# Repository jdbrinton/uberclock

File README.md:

# UberClock PCB
This is the PCB design for the Crystal Filter for the UberClock multi-mode oscillator.

To download gerber files, schematics, or other documentation, see [Latest Release](https://github.com/jdbrinton/uberclock/releases).

# Details
Board dimensions: 100x100mm

Tools: Altium Designer Professional (23.11.1)

# Errata
1. See [issue #1](https://github.com/jdbrinton/uberclock/issues/1) for details and resolution. Crystal resonator footprint wrong. Pin numbers are mirrored.

# Measurements

Measurements taken on NanoVNA V2 (https://nanorfe.com/nanovna-v2.html)

# Sponsor

This work received donation from: https://nlnet.nl/project/uberClock/

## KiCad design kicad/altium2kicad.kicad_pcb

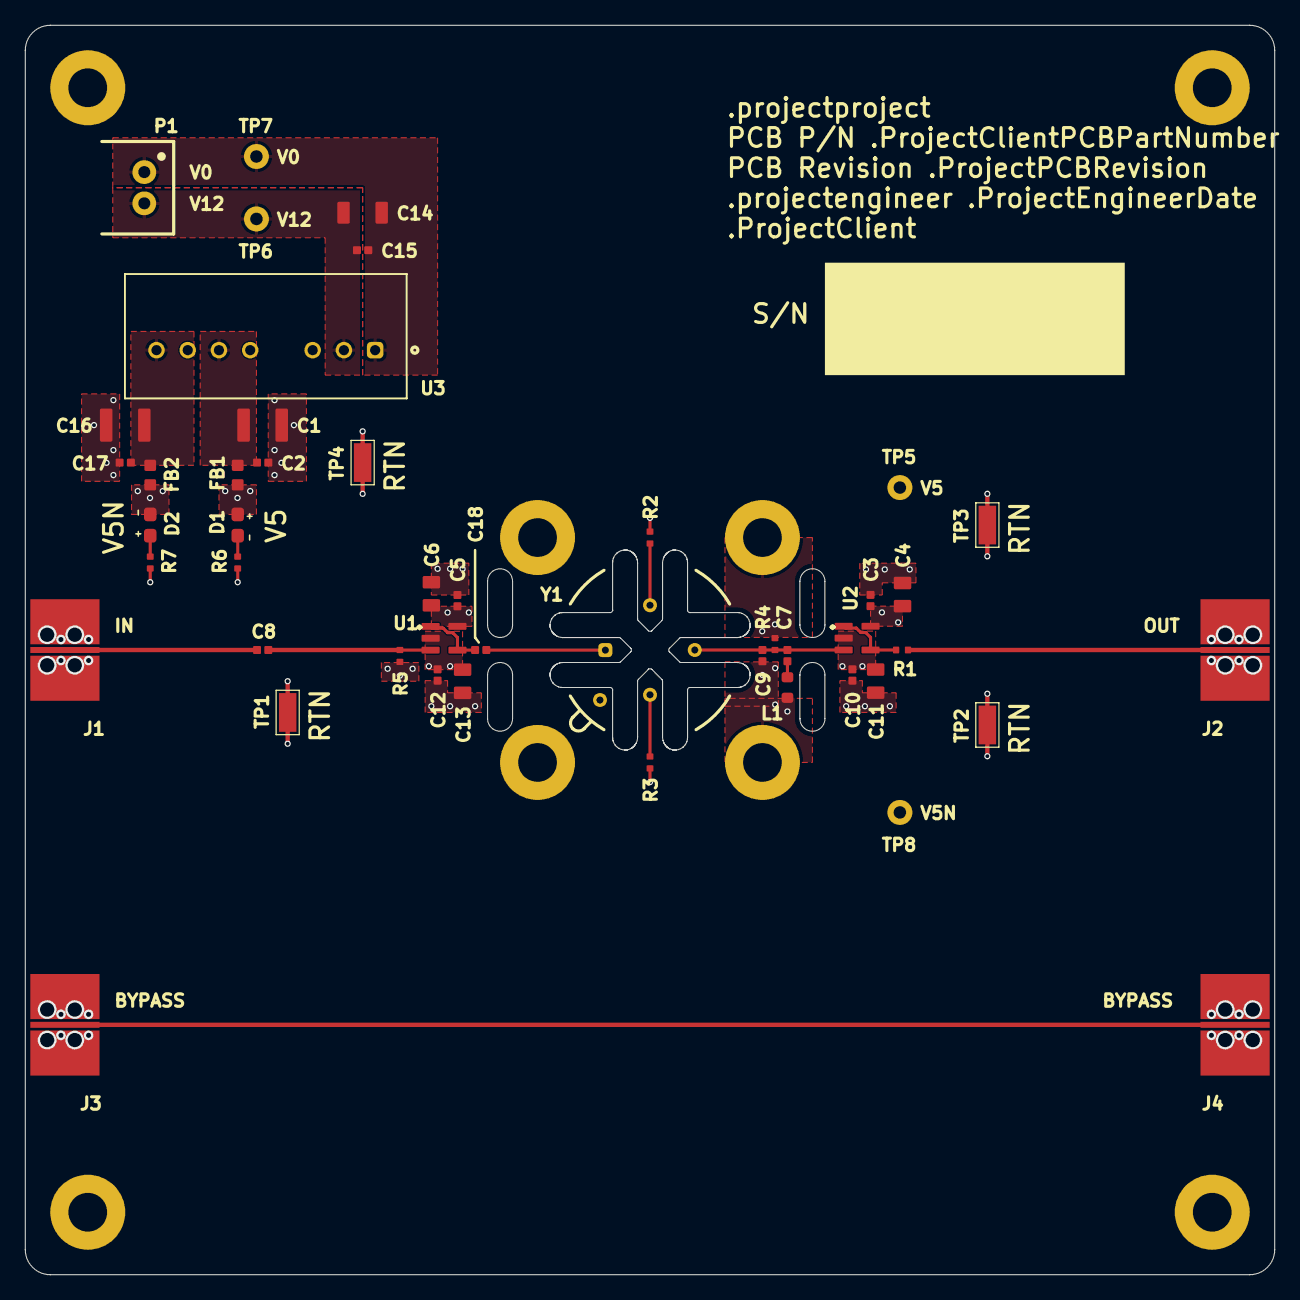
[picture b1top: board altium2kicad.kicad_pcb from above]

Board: 4 copper layers, 100.0 x 100.0 mm, 55 parts (0 on the bottom side), 20 nets.

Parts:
C1, C16: CGA6P1X7S1A476M250AC; CAPC3225X25N
C2, C3, C5, C8, C10, C12, C15, C17, C18: CGA2B3X7R1V104K050BB; CAPC1005X05N
C4, C6, C11, C13: CGA4J3X5R1E475K125AB; CAPC2012X125N
C7, C9: CGA2B2C0G1H180J050BA; CAPC1005X05N
C14: CGA5L3X5R1V106M160AB; CAPC3216X16N
D1, D2: LTST-C191KGKT; 0603_LED
FB1, FB2: BLM18AG102SN1; INDC1608X08N
J1, J2, J3, J4: #NAME?; 901-10510-1
L1: LQW18AN68NJ00D; INDC1608X08N
M1, M2, M3, M4, M5, M6, M7, M8: MOUNTM3
P1: S2B-XH-A
R1, R5: ERJ-2RKF49R9X; RESC1005X035N
R2, R3, R4: ERJ-2RKF1004X; RESC1005X035N
R6, R7: ERJ-2RKF1001X; RESC1005X035N
TP1, TP2, TP3, TP4: 5015
TP5: #NAME?; 5003
TP6: #NAME?; 5000
TP7: #NAME?; 5001
TP8: #NAME?; 5004
U1, U2: AD8065ARTZ-REEL7; SOT23-5
U3: DPBW03F-05; SPBW03F-05_MWU
Y1: 311205346

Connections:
BYPASS: J3.1, J4.1
NetC1_2: C1.2, C2.1, FB1.1, U3.6
NetC7_1: C7.1, L1.1
NetC8_1: C8.1, R5.2, U1.3
NetC16_2: C16.2, C17.1, FB2.1, U3.8
NetD1_2: D1.2, R6.1
NetD2_1: D2.1, R7.1
NetR2_1: R2.1, Y1.2
NetR3_1: R3.1, Y1.4
RTN: C1.1, C2.2, C3.2, C4.1, C5.2, C6.1, C9.1, C10.2, C11.1, C12.2, C13.1, C16.1, C17.2, J1.2, J2.2, J3.2, J4.2, L1.2, M1.1, M2.1, M3.1, M4.1, M5.1, M6.1, M7.1, M8.1, R2.2, R3.2, R4.1, R5.1, R6.2, R7.2, TP1.1, TP2.1, TP3.1, TP4.1, U3.7, Y1.5
SIN: C8.2, J1.1
SIN_T: C18.2, U1.1, U1.4
SOUT: J2.1, R1.1
SOUT_T: R1.2, U2.1, U2.4
V0: C14.1, C15.2, P1.1, TP7.1, U3.1
V5: C3.1, C4.2, C5.1, C6.2, D1.1, FB1.2, TP5.1, U1.5, U2.5
V5N: C10.1, C11.2, C12.1, C13.2, D2.2, FB2.2, TP8.1, U1.2, U2.2
V12: C14.2, C15.1, P1.2, TP6.1, U3.2
XIN: C18.1, Y1.1
XOUT: C7.2, C9.2, R4.2, U2.3, Y1.3

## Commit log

2025-01-20 updated 3d model of resonator
2025-02-24 Create LICENSE
2025-02-24 Adding photo
2025-02-24 adding VNA measurements
2025-04-07 converting to kicad
